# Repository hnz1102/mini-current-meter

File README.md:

<div align="center">
  <h1><code>Mini Current Meter</code></h1>
  
</div>

# Mini Current Meter - Mini Size High-resolution Digital Power Monitor and Logger

This tool provides a logging function that captures data on voltage, current and power consumption. Voltage input range is from 0 to 35V, maximum current input is 10A. 

# Features

**High-resolution** - By using Texas Instruments INA228 IC - 20-bit delta-sigma ADC, it can obtain measurement data with 195µV bus voltage and 163.84mV shunt voltage resolution.

**Microcontroller on board** - No need for a client PC when measuring. Data is sent directly to the server.

**Transfer measurement data via WiFi** - This logger can transfer data to a Linux PC via WiFi network and you can view the dashboard graph in InfluxDB.

**Calibration Function** - Built-in calibration functionality with persistent storage. Long press the center button for 2+ seconds to perform automatic calibration that corrects voltage and current measurement offsets. Calibration results are automatically saved to non-volatile storage and restored on power-up.

**Change Channel** - This logger allows you to change the measurement channel by pushing the center button with a pin. Once you push the center button, the channel will change to the next channel. The channel cycles through 1, 2, 3, 4, and back to 1.

**Battery Powered** - Uses LiPo battery. It can run for 12 hours on a single charge. The battery is charged via USB Type-C port.

**Mini Size** - The dimensions are 37mm(W) x 67mm(D) x 55mm(H). It can be used in various locations.

# How to Use the Logger

This meter has a pin socket with three pins: VBUS/VIN+, GND, and VIN-. The VBUS/VIN+ pin is connected to the voltage input or the current input. The GND pin is connected to the ground of the voltage or current input. The VIN- pin is connected to the load side of the voltage or current input.

DO NOT CONNECT WITH REVERSE POLARITY BETWEEN VBUS/VIN+ AND GND. IF CONNECTED INCORRECTLY, THE ADC IC WILL BE DAMAGED.

The measurement interval time is fixed at 100ms. Each measurement data is sent to the server every 1 second.

The display shows the current voltage, current, power consumption, battery voltage, buffer consumption, WiFi connection status, and channel number.
If the WiFi Access Point cannot establish a connection, the display will not show the WiFi indicator. If voltage is measured while WiFi is not connected, the data is stored in the logger's internal memory buffer. The buffer that is not being sent to the server is indicated by a buffer bar on the display. When the buffer is full (the bar reaches the right edge of the display), measurement stops automatically. When WiFi is connected and data is transmitted to the server, the buffer bar shrinks to the left. When the buffer is full and measurement is stopped, measurement will resume automatically after the buffer drops below 50%.

If you send data to the server, you can see real-time data using the Dashboard in [InfluxDB](https://www.influxdata.com/influxdb/). If you have 3 meters, you can view data on the dashboard with different channels simultaneously.

These meters are small and light, so you can use them in various locations. For example, you can use them to measure circuit current on your breadboard, or you can measure the current at each measurement point on your breadboard circuit. 

To charge the battery, simply connect to a USB Type-C port from a bus-powered USB port. During charging, the CHG LED is RED. After charging is complete, the FUL LED is GREEN and charging will stop automatically. However,

DO NOT CONTINUE CHARGING IF THE BATTERY IS FULL FOR A LONG TIME.

# Calibration Function

The Mini Current Meter includes built-in calibration functionality to correct measurement offsets and improve accuracy.

## How to Perform Calibration

1. **Prepare for calibration**: Ensure no current is flowing through the shunt resistor and no voltage is applied to the measurement inputs (VBUS/VIN+ and GND should be at the same potential).

2. **Start calibration**: Press and hold the center button for **2-5 seconds**. The display will show "Calibrating..." message.

3. **Calibration process**: The device automatically takes 300 samples over 3 seconds to calculate average voltage and current offsets.

4. **Completion**: When calibration is complete, the display will show "Calibration OK" for 2 seconds, and the offset values will be automatically saved to non-volatile storage.

## Button Functions

- **Short press** (< 2 seconds): Change measurement channel (1-4)
- **Long press** (2+ seconds): Perform calibration

## Calibration Features

- **Automatic offset correction**: Calibration corrects both voltage and current measurement offsets
- **Persistent storage**: Calibration results are automatically saved to NVS (Non-Volatile Storage) and restored on power-up
- **High accuracy**: Uses 300-sample averaging for precise offset calculation
- **User feedback**: Real-time status display during calibration process

## When to Calibrate

- **Initial setup**: Perform calibration when first using the device
- **Temperature changes**: Recalibrate if operating temperature changes significantly
- **Accuracy concerns**: If measurements appear to have a systematic offset
- **After firmware updates**: Recalibration recommended after major firmware changes

**Note**: Always ensure zero current flow and zero voltage difference during calibration for best results.

# Recent Updates

## Version 2025.08 - Calibration and Accuracy Improvements

- **Added calibration functionality**: Built-in calibration system with persistent storage
- **Improved measurement accuracy**: Automatic offset correction for voltage and current readings
- **Enhanced button handling**: Added debouncing and multi-function button support (channel change, calibration, reset)
- **NVS integration**: Calibration data automatically saved and restored across power cycles
- **User interface improvements**: Real-time calibration status display and user feedback
- **Error correction**: Fixed voltage measurement accuracy issues and ADC offset handling

# How to Build from Code and Install to the Unit

Using Ubuntu 22.04 LTS

1. Install Rust Compiler
```bash
sudo apt update && sudo apt -y install git python3 python3-pip gcc build-essential curl pkg-config libudev-dev libtinfo5 clang libclang-dev llvm-dev udev libssl-dev python3.10-venv
curl --proto '=https' --tlsv1.2 -sSf https://sh.rustup.rs | sh
```

select No.1

After installation, you need to set the environment variable for Rust.
Add the following line to your shell configuration file (e.g., `~/.bashrc`, `~/.zshrc`, etc.):
```bash
source "$HOME/.cargo/env"
```

2. Install toolchain for ESP32-C3
```bash
cargo install ldproxy
cargo install espup
cargo install cargo-espflash
```

At this time (2025-07-25), espup cannot be compiled. If you get an error, please use the following command to install the toolchain.
```bash
cargo install cargo-binstall
cargo binstall espup
```

```bash
espup install
espup update
```

Then, run the following command to set the environment for the ESP32-C3 toolchain:
```bash
. ./export-esp.sh
```

3. Add UDEV rules
```bash
sudo sh -c 'echo "SUBSYSTEMS==\"usb\", ATTRS{idVendor}==\"303a\", ATTRS{idProduct}==\"1001\", MODE=\"0666\"" > /etc/udev/rules.d/99-esp32.rules'
sudo udevadm control --reload-rules
sudo udevadm trigger
```

4. Download Mini Current Meter code
```bash
git clone https://github.com/hnz1102/mini-current-meter.git
cd mini-current-meter/code
``` 
5. Setting WiFi SSID, Password, and InfluxDB Server IP Address

You need to set the WiFi SSID, password, and InfluxDB server IP address in the configuration file.
You can find the configuration file 'cfg.toml.samp' in the `code` directory. You need to copy this file to `cfg.toml` and edit it.

```bash
nano code/cfg.toml

[mini-current-meter]
wifi_ssid = "XXXXXXXXXXXX"  # Set your WiFi SSID.
wifi_psk = "XXXXXXXXXXXXX"  # Set your WiFi Password.
shunt_resistance = "0.005"
influxdb_server = "<IP Address>:8086"  # Set your InfluxDB server IP address.
influxdb_api_key = "<API_KEY>" # Set your InfluxDB API Key.
influxdb_api = "/api/v2/write?org=<ORG>&bucket=LOGGER&precision=ns" # Set your InfluxDB API URL. You must set <ORG> same as Initial Organization Name.
influxdb_tag = "ch"
influxdb_measurement = "minicurrent"
max_records = "1023"
```

6. Connecting the Board and Setting Device and Toolchain
```bash
Connect the mini-current-meter via USB to this build code PC. Then, 
$ cargo espflash board-info
select /dev/ttyACM0
Chip type:         esp32c3 (revision v0.4)
Crystal frequency: 40MHz
Flash size:        4MB
Features:          WiFi, BLE
MAC address:       xx:xx:xx:xx:xx:xx

$ rustup component add rust-src --toolchain nightly-2023-06-10-x86_64-unknown-linux-gnu
```

7. Build Code and Write to Flash
```bash
$ cargo espflash flash --release --monitor
App/part. size:    964,240/3,145,728 bytes, 30.23%
[00:00:00] [========================================]      12/12      0x0                                                                       
[00:00:00] [========================================]       1/1       0x8000                                                                    
[00:00:11] [========================================]     546/546     0x10000                                                                   [2023-11-11T10:17:05Z INFO ] Flashing has completed!

Automatically boots!
```
# How to Install InfluxDB

1. Download [InfluxDB](https://docs.influxdata.com/influxdb/v2.7/install/?t=Linux) and Install
```bash
$ wget https://dl.influxdata.com/influxdb/releases/influxdb2-2.7.0-amd64.deb
$ sudo dpkg -i influxdb2-2.7.0-amd64.deb
$ sudo service influxdb start
```

2. Configure InfluxDB

```
Connect to 'http://<InfluxDB installed PC Address>:8086'
```
Click `GET STARTED` and set `Username`, `Password`, `Initial Organization Name`, and `Initial Bucket Name`
|Term|Value|
|---|---|
|Username|Set login username as InfluxDB administrator web console|
|Password|Set login password as InfluxDB administrator web console|
|Initial Organization Name| Organization Name ex. ORG|
|Initial Bucket Name| LOGGER |

After setting these, click `CONTINUE`.

3. Copy the Operator API Token

You can see the operator API token in the browser. YOU WON'T BE ABLE TO SEE IT AGAIN!
If you want to get a new API token, click `API Tokens` menu from `Sources` Icon, then click `GENERATE API TOKEN` and select `All access token`, click `Save`.
You can see the new API token and copy it.
After copying the token, click `CONFIGURE LATER`.

4. Import the Dashboard Template

Click the `Dashboard` icon, and select `Import Dashboard` from the `CREATE DASHBOARD` menu.

Drop the `mini-current-meter/dashboard/mini-current-meter.json` file to `Drop a file here`, then click `IMPORT JSON AS DASHBOARD`.

You can see the `Mini Current Meter Dashboard` panel on the Dashboards page.

Click this panel, and you can see the Mini Current Meter Dashboard.

If you want to customize the dashboard design, click the configure mark. You can change the graph design.

6. Start Mini Current Meter Logging and Send Data

Turn on the power switch. Logging data will be sent to InfluxDB. You can see the data on the dashboard.

## Schematic, PCB Gerber and Container 3D Data

There is schematic data in the hardware directory including 3D printing data as 3MF format files. 

## LICENSE
This source code is licensed under MIT. Other Hardware Schematic documents are licensed under CC-BY-SA V4.0.

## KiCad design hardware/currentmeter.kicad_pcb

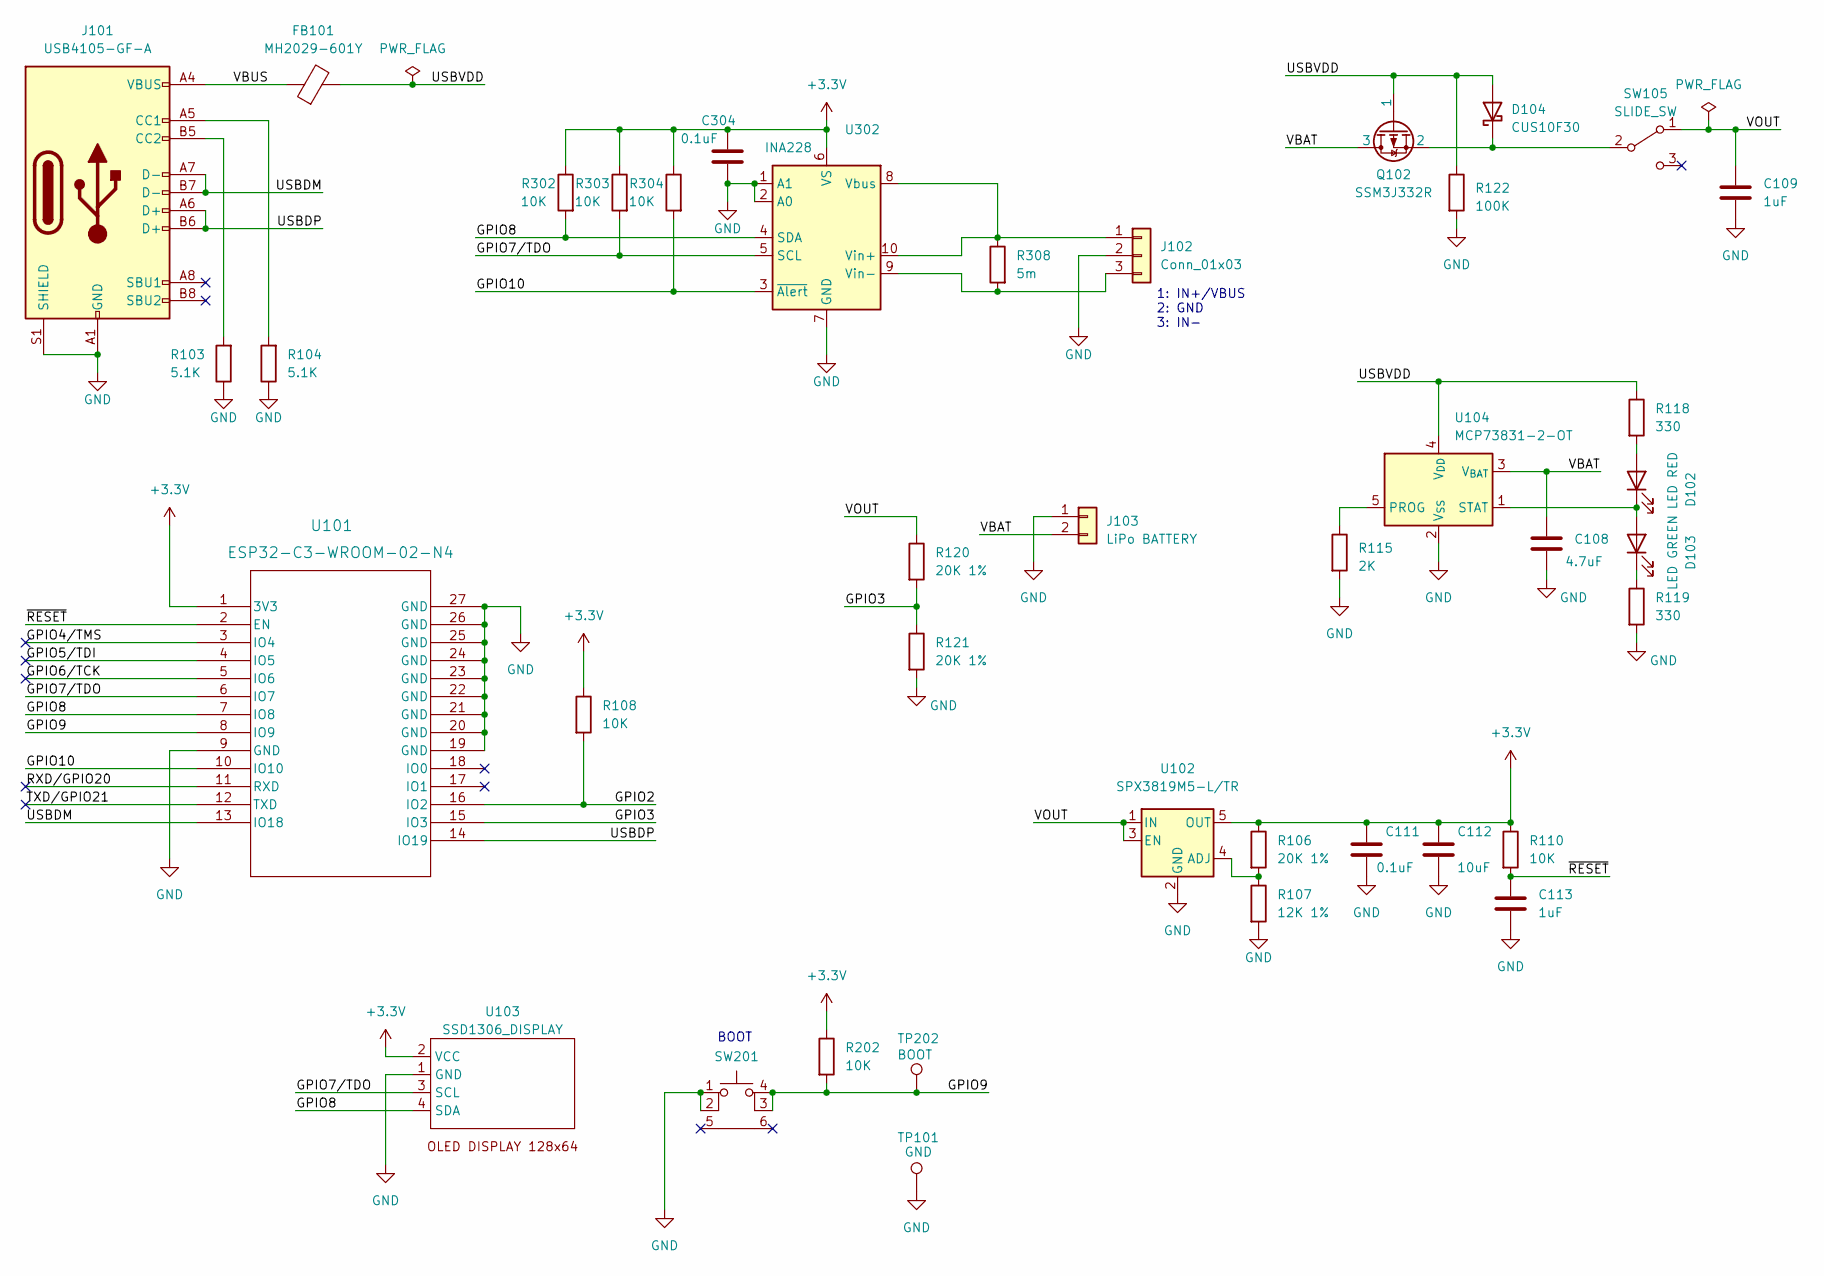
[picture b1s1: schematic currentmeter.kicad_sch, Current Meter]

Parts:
C108: 4.7uF; C_0805_2012Metric; digikey 1276-1244-1-ND
C109, C113: 1uF; C_0805_2012Metric; digikey 1276-1029-1-ND
C111, C304: 0.1uF; C_0603_1608Metric; digikey 311-1088-1-ND
C112: 10uF; C_0805_2012Metric; digikey 587-1300-1-ND
D102: LED RED; LED_0603_1608Metric_Pad1.05x0.95mm_HandSolder; digikey 3147-B1931URO-20D000114U1930CT-ND
D103: LED GREEN; LED_0603_1608Metric_Pad1.05x0.95mm_HandSolder; digikey 3147-B1911PG--20D000514U1930CT-ND
D104: CUS10F30; D_SOD-323_HandSoldering; digikey CUS10F30H3FCT-ND
FB101: MH2029-601Y; L_0805_2012Metric; digikey MH2029-601YCT-ND
J101: USB4105-GF-A; USB_C_5077CR-16-SMC2-BK-TR; digikey 2073-USB4105-GF-ACT-ND
J102: Conn_01x03; PinSocket_1x03_P2.54mm_Vertical
J103: LiPo BATTERY; JST_PH_B2B-PH-K_1x02_P2.00mm_Vertical; digikey 455-1704-ND, Battey: https://www.amazon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
Q102: SSM3J332R; SOT-23; digikey 4518-SSM3J332RCT-ND
R103, R104: 5.1K; R_0603_1608Metric; digikey 311-5.10KHRCT-ND
R106, R120, R121: 20K 1%; R_0603_1608Metric; digikey 311-20.0KHRCT-ND
R107: 12K 1%; R_0603_1608Metric; digikey 311-12.0KHRCT-ND
R108, R110, R202, R302, R303, R304: 10K; R_0603_1608Metric; digikey 311-10KGRCT-ND
R115: 2K; R_0603_1608Metric; digikey 311-2.0KGRCT-ND
R118, R119: 330; R_0603_1608Metric; digikey 311-330GRCT-ND
R122: 100K; R_0603_1608Metric; digikey RMCF0603FT100KCT-ND
R308: 5m; R_2512_6332Metric_Pad1.40x3.35mm_HandSolder; digikey 4506-PEWF2512D5L00Q9CT-ND
SW105: SLIDE_SW; SLIDE_SW_IS1235-G; digikey SLIDE_SW_IS1235-G https://akizukidenshi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
SW201: 3.5x2.6 Tact SW; WS-TASV SMT Tact Switch; digikey 732-435151014824CT-ND
TP101: GND; TestPoint_Pad_D1.0mm
TP202: BOOT; TestPoint_Pad_D1.0mm
U101: ESP32-C3-WROOM-02-N4; IC18_ESP32-C3-WROOM-02-N4_EXP; digikey 1965-ESP32-C3-WROOM-02-N4CT-ND
U102: SPX3819M5-L/TR; SOT-23-5; digikey 1016-1871-1-ND
U103: SSD1306_DISPLAY; OLED I2C DISPLAY
U104: MCP73831-2-OT; SOT-23-5
U302: INA228; VSSOP-10_3x3mm_P0.5mm; digikey 296-INA228AIDGSRCT-ND

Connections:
+3.3V: C111.1, C112.1, C304.1, R106.1, R108.1, R110.1, R202.1, R302.1, R303.1, R304.1, U101.1 (3V3), U102.5 (OUT), U103.2 (VCC), U302.6 (VS)
/GPIO2: R108.2, U101.16 (IO2)
/GPIO3: R120.2, R121.1, U101.15 (IO3)
/GPIO4/TMS: U101.3 (IO4)
/GPIO5/TDI: U101.4 (IO5)
/GPIO6/TCK: U101.5 (IO6)
/GPIO7/TDO: R303.2, U101.6 (IO7), U103.3 (SCL), U302.5 (SCL)
/GPIO8: R302.2, U101.7 (IO8), U103.4 (SDA), U302.4 (SDA)
/GPIO9: R202.2, SW201.3 (K), SW201.4 (A), TP202.1, U101.8 (IO9)
/GPIO10: R304.2, U101.10 (IO10), U302.3 (~Alert)
/RXD/GPIO20: U101.11 (RXD)
/TXD/GPIO21: U101.12 (TXD)
/USBDM: J101.A7 (D-), J101.B7 (D-), U101.13 (IO18)
/USBDP: J101.A6 (D+), J101.B6 (D+), U101.14 (IO19)
/USBVDD: D104.2 (A), FB101.2, Q102.1, R118.1, R122.1, U104.4 (V_{DD})
/VBAT: C108.1, J103.2, Q102.3, U104.3 (V_{BAT})
/VBUS: FB101.1, J101.A4 (VBUS), J101.A9 (VBUS), J101.B4 (VBUS), J101.B9 (VBUS)
/VOUT: C109.1, R120.1, SW105.1 (A), U102.1 (IN), U102.3 (EN)
/~RESET: C113.1, R110.2, U101.2 (EN)
GND: C108.2, C109.2, C111.2, C112.2, C113.2, C304.2, J101.A1 (GND), J101.A12 (GND), J101.B1 (GND), J101.B12 (GND), J101.S1 (SHIELD), J102.2, J103.1, R103.1, R104.1, R107.2, R115.2, R119.2, R121.2, R122.2, SW201.1, SW201.2, TP101.1, U101.9 (GND), U101.19 (GND), U101.20 (GND), U101.21 (GND), U101.22 (GND), U101.23 (GND), U101.24 (GND), U101.25 (GND), U101.26 (GND), U101.27 (GND), U102.2 (GND), U103.1 (GND), U104.2 (V_{SS}), U302.1 (A1), U302.2 (A0), U302.7 (GND)
unnamed: D102.2 (A), R118.2
unnamed: D102.1 (K), D103.2 (A), U104.1 (STAT)
unnamed: D103.1 (K), R119.1
unnamed: D104.1 (K), Q102.2, SW105.2 (B)
unnamed: J101.A5 (CC1), R104.2
unnamed: J101.B5 (CC2), R103.2
unnamed: J102.1, R308.1, U302.8 (Vbus), U302.10 (Vin+)
unnamed: J102.3, R308.2, U302.9 (Vin-)
unnamed: R106.2, R107.1, U102.4 (ADJ)
unnamed: R115.1, U104.5 (PROG)

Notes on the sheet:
BOOT
1: IN+/VBUS 2: GND 3: IN-

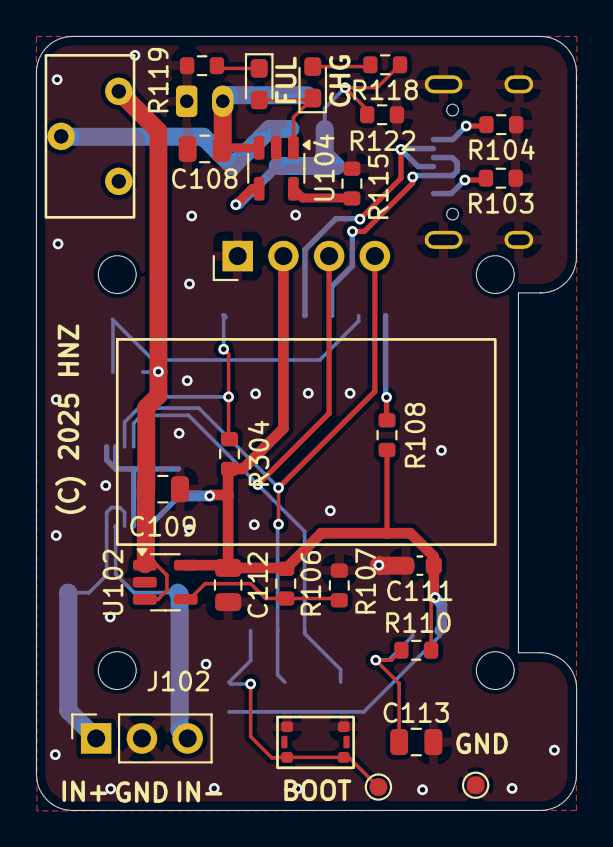
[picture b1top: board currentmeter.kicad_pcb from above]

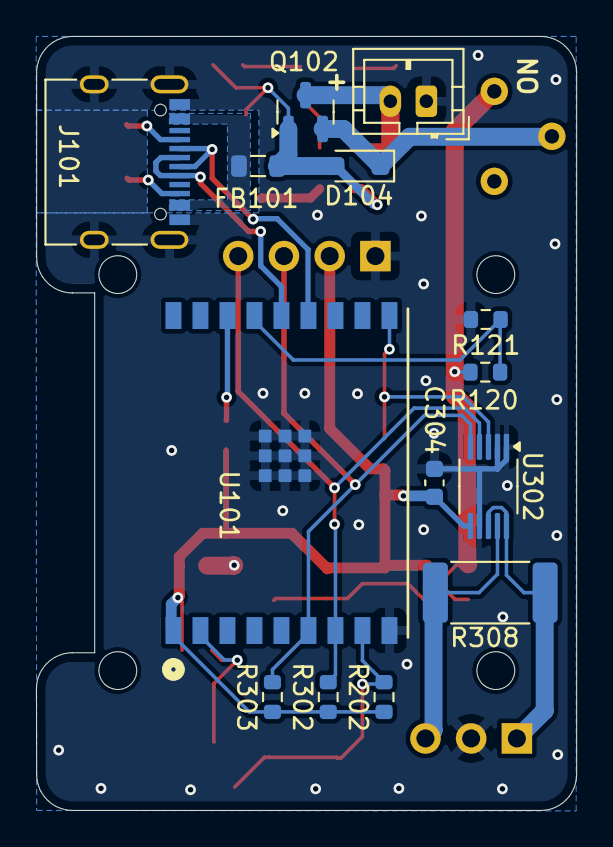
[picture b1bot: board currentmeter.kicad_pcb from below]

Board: 2 copper layers, 30.0 x 43.0 mm, 40 parts (14 on the bottom side), 25 nets.

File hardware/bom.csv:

"Reference","Value","Footprint","Qty","digikey","DNP"
"C108","4.7uF","Capacitor_SMD:C_0805_2012Metric","1","1276-1244-1-ND",""
"C109,C113","1uF","Capacitor_SMD:C_0805_2012Metric","2","1276-1029-1-ND",""
"C111,C304","0.1uF","Capacitor_SMD:C_0603_1608Metric","2","311-1088-1-ND",""
"C112","10uF","Capacitor_SMD:C_0805_2012Metric","1","587-1300-1-ND",""
"D102","LED RED","LED_SMD:LED_0603_1608Metric_Pad1.05x0.95mm_HandSolder","1","3147-B1931URO-20D000114U1930CT-ND",""
"D103","LED GREEN","LED_SMD:LED_0603_1608Metric_Pad1.05x0.95mm_HandSolder","1","3147-B1911PG--20D000514U1930CT-ND",""
"D104","CUS10F30","Diode_SMD:D_SOD-323_HandSoldering","1","CUS10F30H3FCT-ND",""
"FB101","MH2029-601Y","Inductor_SMD:L_0805_2012Metric","1","MH2029-601YCT-ND",""
"J101","USB4105-GF-A","Lib:USB_C_5077CR-16-SMC2-BK-TR","1","2073-USB4105-GF-ACT-ND",""
"J102","Conn_01x03","Connector_PinSocket_2.54mm:PinSocket_1x03_P2.54mm_Vertical","1","https://akizukidenshi.com/catalog/g/g110098/",""
"J103","LiPo BATTERY","Connector_JST:JST_PH_B2B-PH-K_1x02_P2.00mm_Vertical","1","455-1704-ND, Battey:  https://www.amazon.com/EEMB-Battery-Rechargeable-Connector-C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",""
"Q102","SSM3J332R","Package_TO_SOT_SMD:SOT-23","1","4518-SSM3J332RCT-ND",""
"R103,R104","5.1K","Resistor_SMD:R_0603_1608Metric","2","311-5.10KHRCT-ND",""
"R106,R120,R121","20K 1%","Resistor_SMD:R_0603_1608Metric","3","311-20.0KHRCT-ND",""
"R107","12K 1%","Resistor_SMD:R_0603_1608Metric","1","311-12.0KHRCT-ND",""
"R108,R110,R202,R302,R303,R304","10K","Resistor_SMD:R_0603_1608Metric","6","311-10KGRCT-ND",""
"R115","2K","Resistor_SMD:R_0603_1608Metric","1","311-2.0KGRCT-ND",""
"R118,R119","330","Resistor_SMD:R_0603_1608Metric","2","311-330GRCT-ND",""
"R122","100K","Resistor_SMD:R_0603_1608Metric","1","RMCF0603FT100KCT-ND",""
"R308","5m","Resistor_SMD:R_2512_6332Metric_Pad1.40x3.35mm_HandSolder","1","4506-PEWF2512D5L00Q9CT-ND ",""
"SW105","SLIDE_SW","Lib:SLIDE_SW_IS1235-G","1","SLIDE_SW_IS1235-G  https://akizukidenshi.com/catalog/g/g115368/",""
"SW201","3.5x2.6 Tact SW","Lib:WS-TASV SMT Tact Switch","1","732-435151014824CT-ND",""
"TP101","GND","TestPoint:TestPoint_Pad_D1.0mm","1","-",""
"TP202","BOOT","TestPoint:TestPoint_Pad_D1.0mm","1","-",""
"U101","ESP32-C3-WROOM-02-N4","Lib:IC18_ESP32-C3-WROOM-02-N4_EXP","1","1965-ESP32-C3-WROOM-02-N4CT-ND",""
"U102","SPX3819M5-L/TR","Package_TO_SOT_SMD:SOT-23-5","1","1016-1871-1-ND",""
"U103","SSD1306_DISPLAY","Lib:OLED I2C DISPLAY","1","https://akizukidenshi.com/catalog/g/g112031/",""
"U104","MCP73831-2-OT","Package_TO_SOT_SMD:SOT-23-5","1","https://akizukidenshi.com/catalog/g/g113288/",""
"U302","INA228","Package_SO:VSSOP-10_3x3mm_P0.5mm","1","296-INA228AIDGSRCT-ND",""

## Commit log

2025-07-31 Fixed Typo.
2025-08-06 Add gerber file
2025-08-11 Fixed measurement for voltage
2025-08-11 Remove calibration reset function
2025-08-11 Version 0.1.1
2025-08-11 Adjust shunt registance
2025-08-16 Change sampling time and average

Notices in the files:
hardware/currentmeter.kicad_pcb:
(C) 2025 HNZ
hardware/currentmeter.kicad_sch:
(C) 2025 Hiroshi Nakajima
